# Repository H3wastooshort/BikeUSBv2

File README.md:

# BikeUSB v2 *(WIP)*

Ever wanted to charge your phone of your bikes dynamo?
This Project does just that, for cheap (ish).

## Working Principle
The incoming AC voltage from the dynamo gets rectified by 4 shottky-diodes and buffered in a high-capacity capacitor.
Once a sufficient driving speed is reached and the capacitor is charged enough, the ATtiny1616 MCU on the board wakes up.

It measures the frequency of incoming AC voltage, which is corrolated to the driving speed, until it reaches the first threshold.
Once the first threshold is reached, it can be assumed that enough power is available to charge the phone at 2.5W.
The MCU enables the high efficiency DC/DC-Converter IC to generate 5V at the USB Type C Port.
The pull-ups in the FUSB302 IC are set to signal to the attached device that 2.5W (500mA) are available.
This prevents constant starting and stopping of the charging process, which is annoying.
If the frequency is high enough to reach the 5W or 7.5W thresholds, 5W or 7.5W will be signaled via USB C power delivery.

If the device detects a DC source, it enters configuration mode. In configuration mode, the 2 buttons are used to select which threshold to calibrate.
Connecting it back to a bike dynamo, it is now in calibration mode.
The MCU will detect the needed speed to generate enough power for the prev. selected power level by connecting a 3W, 6W, or 9W constant power load and driving at a steadily increasing speed.
Once the PowerGood signal does not drop out for 5 seconds with the load connected, a sufficient speed has been reached and is saved to EEPROM.

## Schematic

## PCB

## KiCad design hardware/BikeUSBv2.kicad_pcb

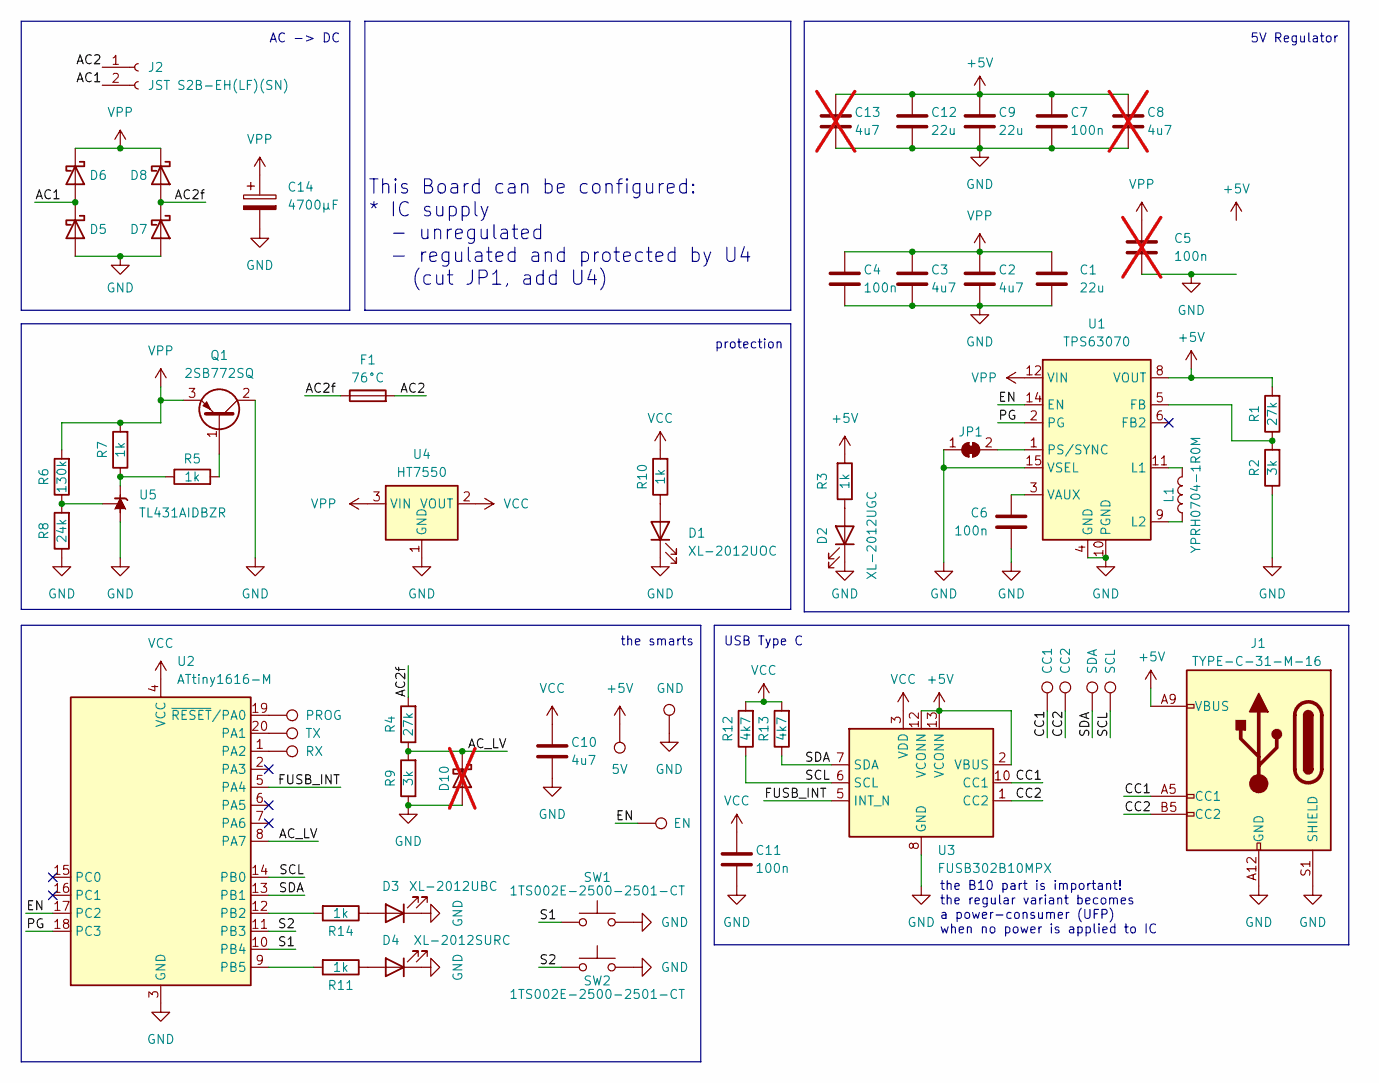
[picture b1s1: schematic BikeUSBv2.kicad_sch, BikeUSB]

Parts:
C1, C9, C12: 22u; C_1206_3216Metric_Pad1.33x1.80mm_HandSolder; LCSC C12891
C2, C3, C10: 4u7; C_0805_2012Metric_Pad1.18x1.45mm_HandSolder; LCSC C1779
C4, C6, C7, C11: 100n; C_0805_2012Metric_Pad1.18x1.45mm_HandSolder; LCSC C1711
C5: 100n; C_0603_1608Metric_Pad1.08x0.95mm_HandSolder; not fitted
C8, C13: 4u7; C_0805_2012Metric_Pad1.18x1.45mm_HandSolder; LCSC C1779; not fitted
C14: 4700µF; CP_Radial_D8.0mm_P5.00mm; LCSC C47893
D1: XL-2012UOC; LED_0805_2012Metric_Pad1.15x1.40mm_HandSolder; LCSC C965813
D2: XL-2012UGC; LED_0805_2012Metric_Pad1.15x1.40mm_HandSolder; LCSC C965815
D3: XL-2012UBC; LED_0805_2012Metric_Pad1.15x1.40mm_HandSolder; LCSC C965817
D4: XL-2012SURC; LED_0805_2012Metric_Pad1.15x1.40mm_HandSolder; LCSC C965812
D5, D6, D7, D8: CMS04(TE12L,Q,M); D_SOD-128; LCSC C603062
D10: D_PowerDI-123; not fitted
F1: 76°C; SETfuse X-Series; Part # X0; LCSC C22396315
J1: TYPE-C-31-M-16; TYPE-C-SMD_TYPE-C-31-M-16; LCSC C283541
J2: JST S2B-EH(LF)(SN); JST_EH_S2B-EH_1x02_P2.50mm_Horizontal; LCSC C514173
JP1: SolderJumper_2_Bridged; SolderJumper-2_P1.3mm_Bridged_RoundedPad1.0x1.5mm
L1: YPRH0704-1R0M; L_7.3x7.3_H4.5; LCSC Part C338840
Q1: 2SB772SQ; SOT-89-3_Handsoldering; LCSC C5158798
R1, R4: 27k; R_0805_2012Metric_Pad1.20x1.40mm_HandSolder; LCSC C375523
R2, R9: 3k; R_0805_2012Metric_Pad1.20x1.40mm_HandSolder; LCSC C218519
R3, R5, R7, R10, R11, R14: 1k; R_0805_2012Metric_Pad1.20x1.40mm_HandSolder; LCSC C110774
R6: 130k; R_0805_2012Metric_Pad1.20x1.40mm_HandSolder; LCSC C2831651
R8: 24k; R_0805_2012Metric_Pad1.20x1.40mm_HandSolder; LCSC C218452
R12, R13: 4k7; R_0805_2012Metric_Pad1.20x1.40mm_HandSolder; LCSC C17673
SW1, SW2: 1TS002E-2500-2501-CT; SW_SPST_CK_RS282G05A3; LCSC C255802
TP1: EN; TestPoint_Pad_D1.0mm
TP2: 5V; TestPoint_Pad_D2.5mm
TP3: GND; TestPoint_Pad_D2.5mm
TP4: PROG; TestPoint_Pad_D2.5mm
TP5: TX; TestPoint_Pad_D2.5mm
TP6: CC1; TestPoint_Pad_D1.5mm
TP7: CC2; TestPoint_Pad_D1.5mm
TP8: SDA; TestPoint_Pad_D1.5mm
TP9: SCL; TestPoint_Pad_D1.5mm
TP10: RX; TestPoint_Pad_D2.5mm
U1: TPS63070; VQFN-HR-15_L3.0-W2.5-P0.50-BL_TPS63070RNMR; LCSC C109322
U2: ATtiny1616-M; VQFN-20-1EP_3x3mm_P0.4mm_EP1.7x1.7mm; LCSC C507118
U3: FUSB302B10MPX; WQFN-14-1EP_2.5x2.5mm_P0.5mm_EP1.45x1.45mm; LCSC C891305
U4: HT7550; SOT-23_Handsoldering; LCSC C5279053
U5: TL431AIDBZR; SOT-23_Handsoldering; LCSC C23892

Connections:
+5V: C7.1, C8.1, C9.1, C12.1, C13.1, J1.A9 (VBUS), J1.B9 (VBUS), R1.2, R3.2, TP2.1, U1.7 (VOUT), U1.8 (VOUT), U3.2 (VBUS), U3.12 (VCONN), U3.13 (VCONN)
/ AC_LV: D10.1 (K), R4.1, R9.2, U2.8 (PA7)
/AC1: D5.1 (K), D6.2 (A), J2.2
/AC2: F1.2, J2.1
/AC2f: D7.1 (K), D8.2 (A), F1.1, R4.2
/CC1: J1.A5 (CC1), TP6.1, U3.10 (CC1), U3.11 (CC1)
/CC2: J1.B5 (CC2), TP7.1, U3.1 (CC2), U3.14 (CC2)
/EN: TP1.1, U1.14 (EN), U2.17 (PC2)
/FUSB_INT: U2.5 (PA4), U3.5 (INT_N)
/PG: U1.2 (PG), U2.18 (PC3)
/S1: SW1.1, U2.10 (PB4)
/S2: SW2.1, U2.11 (PB3)
/SCL: R12.1, TP9.1, U2.14 (PB0), U3.6 (SCL)
/SDA: R13.1, TP8.1, U2.13 (PB1), U3.7 (SDA)
GND: C1.2, C2.2, C3.2, C4.2, C5.2, C6.2, C7.2, C8.2, C9.2, C10.2, C11.2, C12.2, C13.2, C14.2, D1.1 (K), D2.1 (K), D3.1 (K), D4.1 (K), D5.2 (A), D7.2 (A), D10.2 (A), J1.A12 (GND), J1.B12 (GND), J1.S1 (SHIELD), JP1.1 (A), Q1.2 (C), R2.1, R8.1, R9.1, SW1.2, SW2.2, TP3.1, U1.4 (GND), U1.10 (PGND), U1.15 (VSEL), U2.3 (GND), U2.21 (GND), U3.8 (GND), U3.9 (GND), U3.15 (GND), U4.1 (GND), U5.3 (A)
unnamed: D1.2 (A), R10.1
unnamed: D2.2 (A), R3.1
unnamed: D3.2 (A), R14.1
unnamed: D4.2 (A), R11.1
unnamed: JP1.2 (B), U1.1 (PS/SYNC)
unnamed: Q1.1 (B), R5.2
unnamed: R1.1, R2.2, U1.5 (FB)
unnamed: L1.1, U1.11 (L1)
unnamed: L1.2, U1.9 (L2)
unnamed: C6.1, U1.3 (VAUX)
unnamed: TP5.1, U2.20 (PA1)
unnamed: TP10.1, U2.1 (PA2)
unnamed: R14.2, U2.12 (PB2)
unnamed: R11.2, U2.9 (PB5)
unnamed: TP4.1, U2.19 (~RESET/PA0)
unnamed: R5.1, R7.1, U5.1 (K)
unnamed: R6.1, R8.2, U5.2 (REF)
VCC: C10.1, C11.1, R10.2, R12.2, R13.2, U2.4 (VCC), U3.3 (VDD), U3.4 (VDD), U4.2 (VOUT)
VPP: C1.1, C2.1, C3.1, C4.1, C5.1, C14.1, D6.1 (K), D8.1 (K), Q1.3 (E), R6.2, R7.2, U1.12 (VIN), U1.13 (VIN), U4.3 (VIN)

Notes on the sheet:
the smarts
AC -> DC
the B10 part is important! the regular variant becomes a power-consumer (UFP) when no power is applied to IC
USB Type C
5V Regulator
protection
This Board can be configured: * IC supply - unregulated - regulated and protected by U4 (cut JP1, add U4)

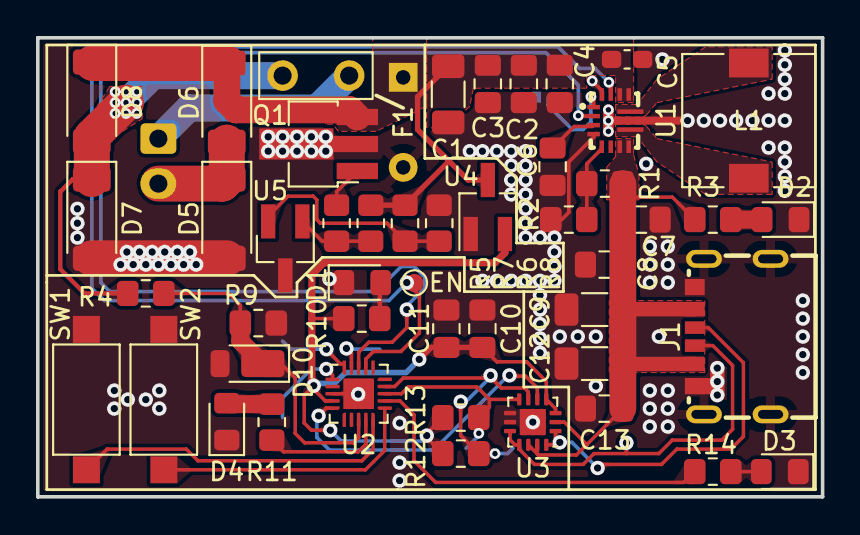
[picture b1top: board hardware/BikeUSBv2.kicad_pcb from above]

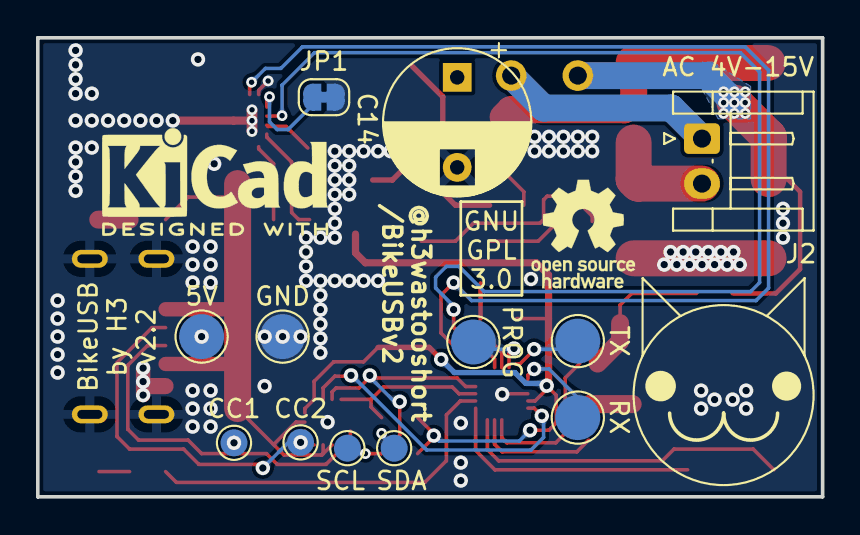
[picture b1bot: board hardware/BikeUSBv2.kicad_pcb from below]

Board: 2 copper layers, 43.6 x 25.5 mm, 61 parts (13 on the bottom side), 34 nets.

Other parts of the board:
CAT**: PCBcat

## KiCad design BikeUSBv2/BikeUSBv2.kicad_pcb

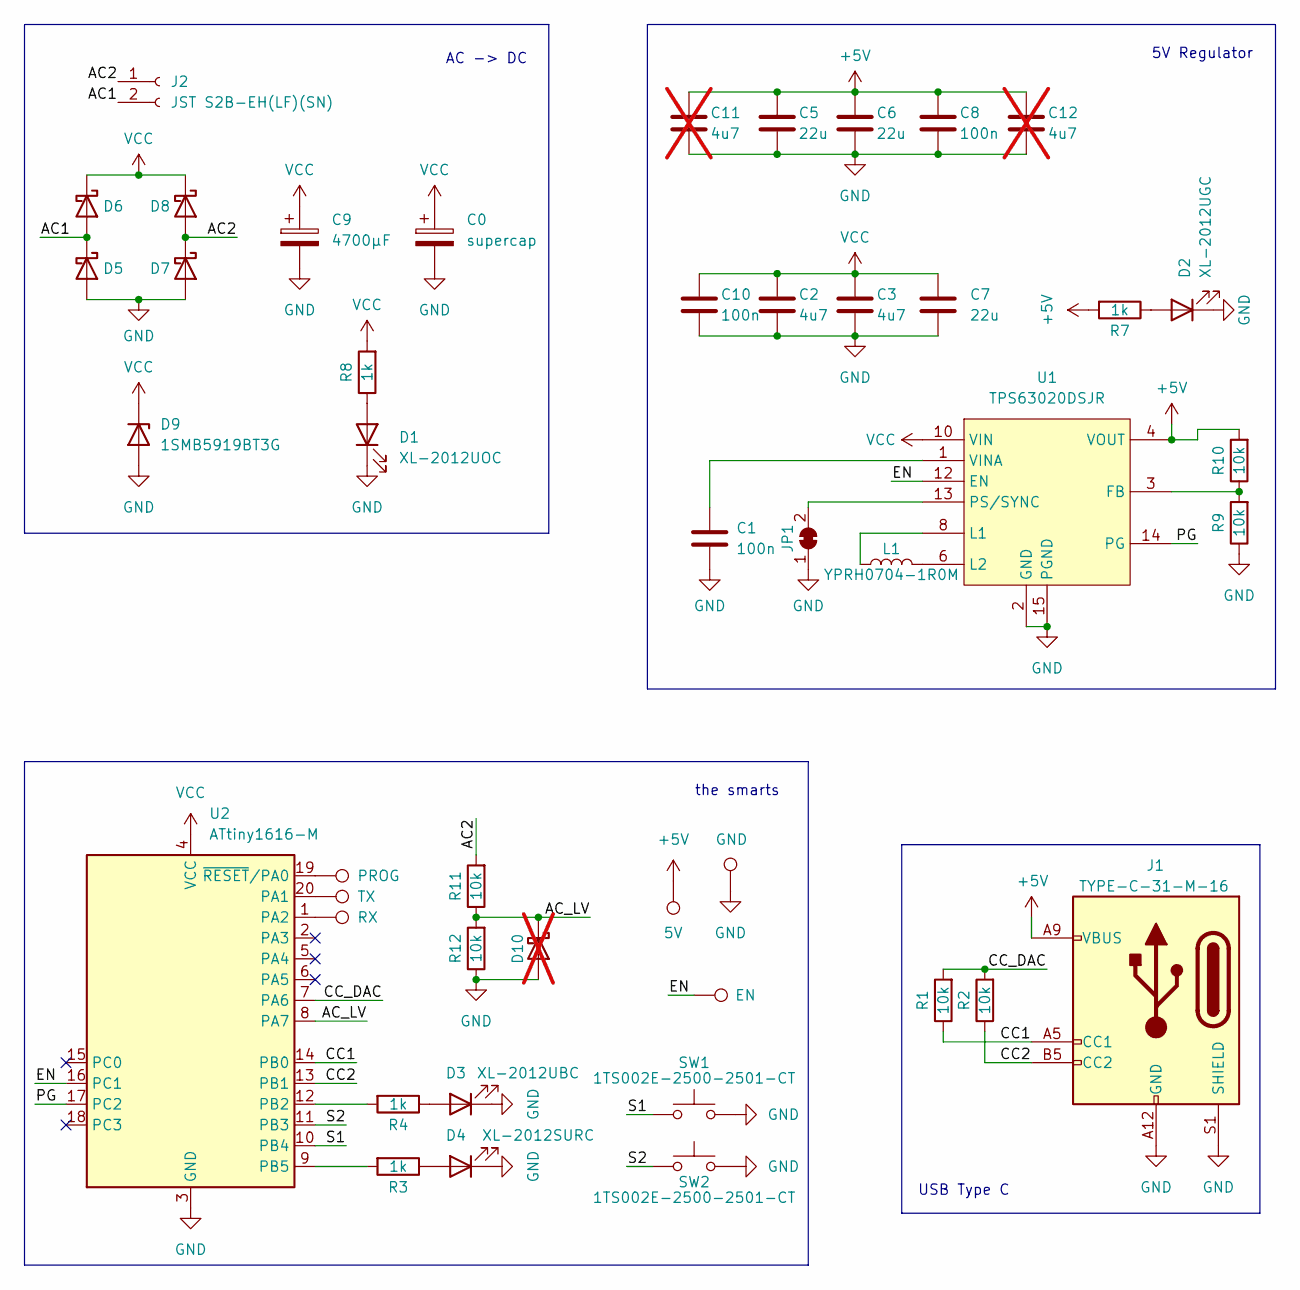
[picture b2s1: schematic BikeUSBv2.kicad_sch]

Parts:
C0: supercap; PinHeader_1x02_P2.54mm_Vertical
C1, C8, C10: 100n; C_0805_2012Metric_Pad1.18x1.45mm_HandSolder; LCSC C1711
C2, C3: 4u7; C_0805_2012Metric_Pad1.18x1.45mm_HandSolder; LCSC C1779
C5, C6, C7: 22u; C_1206_3216Metric_Pad1.33x1.80mm_HandSolder; LCSC C12891
C9: 4700µF; CP_Radial_D8.0mm_P5.00mm; LCSC C47893
C11, C12: 4u7; C_0805_2012Metric_Pad1.18x1.45mm_HandSolder; LCSC C1779; not fitted
D1: XL-2012UOC; LED_0805_2012Metric_Pad1.15x1.40mm_HandSolder; LCSC C965813
D2: XL-2012UGC; LED_0805_2012Metric_Pad1.15x1.40mm_HandSolder; LCSC C965815
D3: XL-2012UBC; LED_0805_2012Metric_Pad1.15x1.40mm_HandSolder; LCSC C965817
D4: XL-2012SURC; LED_0805_2012Metric_Pad1.15x1.40mm_HandSolder; LCSC C965812
D5, D6, D7, D8: CMS04(TE12L,Q,M); D_SOD-128; LCSC C603062
D9: 1SMB5919BT3G; D_SMB-SMC_Universal_Handsoldering; LCSC Part C7422622
D10: D_PowerDI-123; not fitted
J1: TYPE-C-31-M-16; TYPE-C-SMD_TYPE-C-31-M-16; LCSC C283541
J2: JST S2B-EH(LF)(SN); JST_EH_S2B-EH_1x02_P2.50mm_Horizontal; LCSC C514173
JP1: SolderJumper_2_Bridged; SolderJumper-2_P1.3mm_Bridged_RoundedPad1.0x1.5mm
L1: YPRH0704-1R0M; L_7.3x7.3_H4.5; LCSC Part C338840
R1, R2, R9, R10, R11, R12: 10k; R_0805_2012Metric_Pad1.20x1.40mm_HandSolder; LCSC C217770
R3, R4, R7, R8: 1k; R_0805_2012Metric_Pad1.20x1.40mm_HandSolder; LCSC C110774
SW1, SW2: 1TS002E-2500-2501-CT; SW_SPST_CK_RS282G05A3; LCSC C255802
TP1: PROG; TestPoint_Pad_D2.5mm
TP2: GND; TestPoint_Pad_D2.5mm
TP4: TX; TestPoint_Pad_D2.5mm
TP5: RX; TestPoint_Pad_D2.5mm
TP6: 5V; TestPoint_Pad_D2.5mm
TP7: EN; TestPoint_Pad_D2.5mm
U1: TPS63020DSJR; VSON-14_L4.0-W3.0-P0.50-BL-EP_TI_DSJ; LCSC Part C15483
U2: ATtiny1616-M; VQFN-20-1EP_3x3mm_P0.4mm_EP1.7x1.7mm; LCSC C507118

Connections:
+5V: C5.1, C6.1, C8.1, C11.1, C12.1, J1.A9 (VBUS), J1.B9 (VBUS), R7.2, R10.2, TP6.1, U1.4 (VOUT), U1.5 (VOUT)
/ AC_LV: D10.1 (K), R11.1, R12.2, U2.8 (PA7)
/AC1: D5.1 (K), D6.2 (A), J2.2
/AC2: D7.1 (K), D8.2 (A), J2.1, R11.2
/CC1: J1.A5 (CC1), R1.1, U2.14 (PB0)
/CC2: J1.B5 (CC2), R2.1, U2.13 (PB1)
/CC_DAC: R1.2, R2.2, U2.7 (PA6)
/EN: TP7.1, U1.12 (EN), U2.16 (PC1)
/PG: U1.14 (PG), U2.17 (PC2)
/S1: SW1.1, U2.10 (PB4)
/S2: SW2.1, U2.11 (PB3)
GND: C0.2, C1.2, C2.2, C3.2, C5.2, C6.2, C7.2, C8.2, C9.2, C10.2, C11.2, C12.2, D1.1 (K), D2.1 (K), D3.1 (K), D4.1 (K), D5.2 (A), D7.2 (A), D9.2 (A), D10.2 (A), J1.A12 (GND), J1.B12 (GND), J1.S1 (SHIELD), JP1.1 (A), R9.1, R12.1, SW1.2, SW2.2, TP2.1, U1.2 (GND), U1.15 (PGND), U2.3 (GND), U2.21 (GND)
unnamed: D1.2 (A), R8.1
unnamed: D2.2 (A), R7.1
unnamed: D3.2 (A), R4.1
unnamed: D4.2 (A), R3.1
unnamed: JP1.2 (B), U1.13 (PS/SYNC)
unnamed: L1.1, U1.8 (L1), U1.9 (L1)
unnamed: L1.2, U1.6 (L2), U1.7 (L2)
unnamed: R9.2, R10.1, U1.3 (FB)
unnamed: C1.1, U1.1 (VINA)
unnamed: TP4.1, U2.20 (PA1)
unnamed: TP5.1, U2.1 (PA2)
unnamed: R4.2, U2.12 (PB2)
unnamed: R3.2, U2.9 (PB5)
unnamed: TP1.1, U2.19 (~RESET/PA0)
VCC: C0.1, C2.1, C3.1, C7.1, C9.1, C10.1, D6.1 (K), D8.1 (K), D9.1 (K), R8.2, U1.10 (VIN), U1.11 (VIN), U2.4 (VCC)

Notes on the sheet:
the smarts
AC -> DC
USB Type C
5V Regulator

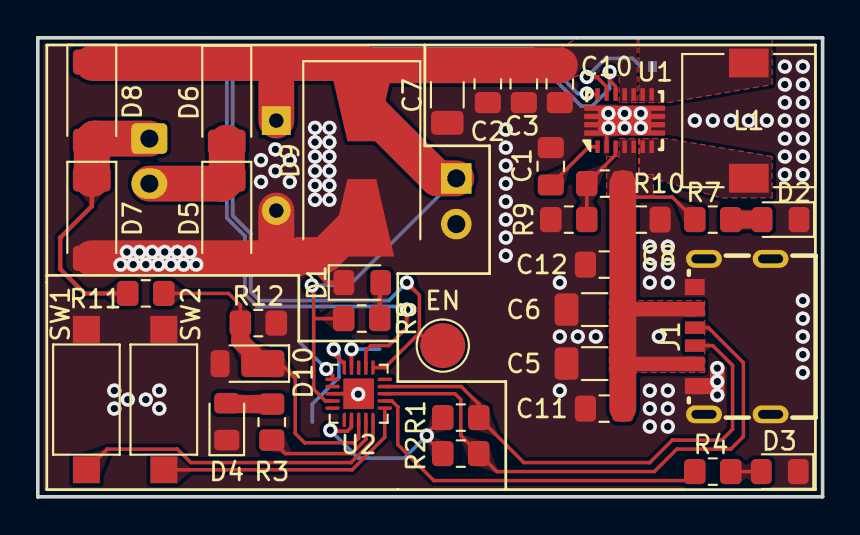
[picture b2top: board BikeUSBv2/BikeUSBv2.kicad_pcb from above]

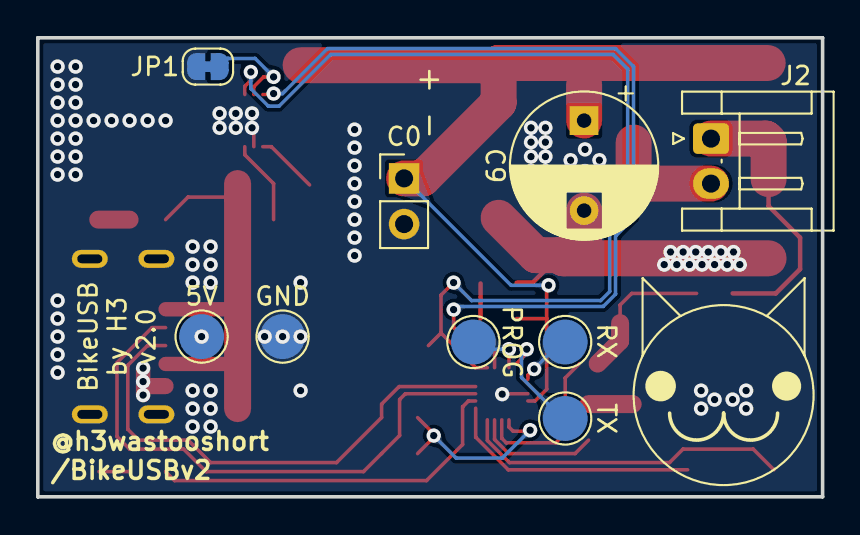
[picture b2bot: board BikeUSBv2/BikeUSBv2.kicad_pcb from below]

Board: 2 copper layers, 43.6 x 25.5 mm, 47 parts (10 on the bottom side), 27 nets.

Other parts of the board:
CAT**: PCBcat

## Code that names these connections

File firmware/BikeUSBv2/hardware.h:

//====PINS====

const uint8_t OUTPUT_ENABLE_PIN = PIN_PC2;
const uint8_t OUTPUT_GOOD_PIN = PIN_PC3;

const uint8_t AC_MEASURE_PIN = PIN_PA7;  //also AINP0, don't change this or AC code must be changed aswell

const uint8_t SDA_PIN = PIN_PC0;
const uint8_t SCL_PIN = PIN_PC1;

const uint8_t FUSB_INT_PIN = PIN_PA4;

#define HAS_FUSB

const uint8_t BTN1_PIN = PIN_PB3;
const uint8_t BTN2_PIN = PIN_PB4;

const uint8_t USR_LED_PIN = PIN_PB5;
const uint8_t PWR_LED_PIN = PIN_PB2;

const uint8_t CC1_PIN = PIN_PB0;
const uint8_t CC2_PIN = PIN_PB1;
const uint8_t CC_DAC_PIN = PIN_PA6;

//====OTHER====

const uint16_t MIN_INPUT_VOLTAGE = 3000;  //in mV, minimum MCU supply voltage needed to allow operation of device
const float FREQ_HYST = 0.1; //10%

//============

void setupHardware() {
  //pin modes
  pinMode(OUTPUT_ENABLE_PIN, OUTPUT);
  digitalWrite(OUTPUT_ENABLE_PIN, LOW);
  pinMode(USR_LED_PIN, OUTPUT);

  //pinMode(AC_MEASURE_PIN, INPUT);
  pinMode(OUTPUT_GOOD_PIN, INPUT_PULLUP);
  pinMode(BTN1_PIN, INPUT_PULLUP);
  pinMode(BTN2_PIN, INPUT_PULLUP);

  pinMode(FUSB_INT_PIN, INPUT_PULLUP);

  //ADC0
  analogReadResolution(10);
  analogReference(INTERNAL2V5);  //set ADC reference to 2.5V as it covers the full range of CC voltages
}

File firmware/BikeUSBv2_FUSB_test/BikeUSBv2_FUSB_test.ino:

#include "../BikeUSBv2/lib/SWI2C_H3/src/SWI2C.h"
#include "../BikeUSBv2/lib/SWI2C_H3/src/SWI2C.cpp"
const uint8_t SDA_PIN = PIN_PC0;
const uint8_t SCL_PIN = PIN_PC1;

const uint8_t FUSB_INT_PIN = PIN_PA4;
SWI2C fusb_i2c(SDA_PIN, SCL_PIN, 0x22);

void setup() {
  // put your setup code here, to run once:
  _PROTECTED_WRITE(WDT.CTRLA, WDT_PERIOD_1KCLK_gc);
  Serial.pins(PIN_PA1, PIN_PA2);
  Serial.begin(9600);
  Serial.println("READY");
}

void loop() {
  // put your main code here, to run repeatedly:
  if (Serial.available()) {
    delay(100);
    switch (Serial.read()) {
      case 'R':
        {
          Serial.println("reading...");
          uint8_t reg = 0, dat = 0xFF;

          reg = Serial.parseInt();

          Serial.printHexln(reg);

          Serial.println(fusb_i2c.readFromRegister(reg, dat) ? "OK" : "FAIL");
          Serial.printHexln(dat);
        }
        break;
      case 'W':
        {
          Serial.println("writing...");

          uint8_t reg = 0, dat = 0;
          reg = Serial.parseInt();
          dat = Serial.parseInt();

          Serial.printHexln(reg);
          Serial.printHexln(dat);

          Serial.println(fusb_i2c.writeToRegister(reg, dat) ? "OK" : "FAIL");
        }
        break;
    }
  }

  __asm__ __volatile__("wdr" ::);
}

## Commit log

2024-01-29 rough schematic
2024-01-29 todia
2024-01-29 some things
2024-01-30 fine, im using an MCU
2024-01-30 group things on PCB
2024-02-02 dont exactly remember what i did here, its from tuesday i think
2024-02-02 placed components, started routing
2024-02-02 routing finished so far
2024-02-03 fix clearances, routing almost done
2024-02-03 idk, forgot to save that
2024-02-03 actually complete routing
2024-02-03 added pcb art, other stuff
2024-02-03 small stuff
2024-02-03 better U1 cap layout
2024-02-03 cleanup
2024-02-03 teardrops
2024-02-03 assign some footprints
2024-02-05 switch diode footprints
2024-02-05 removed teardrops
2024-02-05 added footprint for clamping diode if needed
2024-02-05 reduced component count
2024-02-05 better layout
2024-02-05 stuff
2024-02-05 better inductor track layout
2024-02-05 forgot to rotate the protection silkscreen layer
2024-02-05 oops, those were actually the correct footprints...
2024-02-05 oops 2
2024-02-05 forgot silkscreen
2024-02-05 NPN =/= PNP
2024-02-05 more stuff i forgot
2024-02-05 teardrops + zone fills + other
2024-02-07 update parts
2024-02-07 dingsbumbs
2024-02-07 BOM thing
2024-02-07 all parts selected
2024-02-07 forgot to save PCB
2024-02-08 smaller fixes
2024-02-18 lcsc parts
2024-02-19 half capacitance, but cheaper
2024-02-21 switch CC current source strategy
    these newer attinys have a DAC!
    just use that for the current source!
2024-02-21 push components around, fix lcsc, add cap header
2024-02-22 very small changes
2024-02-22 stop DRC from complaining
2024-02-22 add teardrops
2024-02-27 re-layout parts. routing TBD
2024-02-27 start routing
2024-02-27 route stuff
2024-02-27 routing stuff
2024-03-01 vias, silk
2024-03-15 add docs
2024-03-16 reorder schematic
2024-03-16 fix DRC errors
2024-03-16 auto cleanup
2024-03-16 update docs
2024-03-16 silkscreen
2024-03-17 add name
2024-03-17 rename hardware folder
2024-03-17 add CI
2024-05-05 better auto-img and upload to pages
2024-05-05 fix gha
2024-05-05 fix even dumber issue with gha
2024-05-05 gha names
2024-05-05 fix schematic upload
2024-05-05 fix ghp artifact, split up CI and documentation
2024-05-05 use auto-generated images
2024-05-22 dumb mistake fixed
    i thought the feedback voltage had to be 2.5V at operating voltage. its actually 0.5V
2024-05-22 add proper PD negotiation
2024-05-23 add footprint for ldo-bodge
2024-05-23 oops
2024-05-23 silkscreen cleanup
2024-05-23 clean up teardrops
2024-05-23 different ldo vreg
2024-05-23 switch to FUSB302 without dead-battery charging
2024-05-23 fixup lcsc
2024-05-23 silkscreen fixes
2024-05-23 change OVP protection scheme
2024-05-23 apply changes to PCB
2024-05-23 add info note to sch
2024-05-23 added resistor required in DS
2024-05-23 also render rotating PCB GIF
2024-05-23 remove leftover silkscreen text
2024-05-25 make schematic look nicer
2024-05-25 slight layout improvment
2024-06-12 switch eFuse IC in design
2024-06-13 make U4 optional since new U5 clamps to 5V5
2024-06-13 improve VINA routing
2024-06-13 add therm relief for PTH
2024-06-13 fix stuff like thermals for U5
2024-06-14 layout stuff
2024-06-14 add INT line between U3 and U2
2024-06-14 space EN/PG tracks more + readd teardrops
2024-06-14 forgor
2024-06-14 switch to SOT-23 voltage regulator
2024-06-14 mini silkscreen thing
2024-06-14 add td
2024-06-15 spaghetti diagram
2024-06-15 add submodule for to-be-done FUSB library
2024-06-15 Create led.h
    the most important part of the firmware, the LED blinky stuff!!!!
2024-06-17 move stuff 4 arduino ide
2024-06-17 very very rough idea of how firmware will look
2024-06-17 eeprom check might work now
2024-06-17 wow, this complies
2024-06-20 kinda roughly prototyped MSM
2024-06-20 workin on it
2024-06-20 Summary (required)
2024-06-20 switch I2C library
2024-06-20 Update .gitattributes again, because im stupid
2024-06-20 cal stuff
2024-06-23 experiment with pd stuff
2024-06-23 fix led.h
2024-06-23 fusb code possibly working...
2024-06-23 fgsfd
2024-06-23 change blink patterns
2024-06-27 commit pd friend changes to main program
2024-06-29 pull out src/snk impl. to project code
2024-06-29 pulled out too much
2024-06-29 adapt to pd and msm being indep.
2024-06-29 working on SMs
2024-06-29 cut resistor-based negotiations
    7.5W is pretty unrealistic
    also, I2C needs pullups
2024-06-30 [PCB] change I2C to HW pins
2024-06-30 [PCB] fix Teardrops
2024-06-30 kinda working on it
2024-06-30 interrupt stuff
2024-06-30 pdo stuff
2024-06-30 src stuff
2024-07-01 [PCB] minor layout change
2024-07-01 only enable power after CC pulldowns detected
2024-07-01 [PCB] switch schematic to different VREG
2024-07-01 [PCB] rough layout with new BuckBoost IC
2024-07-01 [PCB] bump version
2024-07-01 [PCB] fix DRC
2024-07-01 [PCB]
    OVP by zener and fuse for now...
2024-07-01 [PCB] different Zener
2024-07-01 [PCB] switch to different protection circuit
2024-07-01 [PCB] add Teardrops
2024-07-01 [PCB] fill in LCSC IDs
2024-07-01 shitty LTSpice sim of voltage limiter
    im assuming the generator won't put out more than 1A
2024-07-01 [PCB] layout less ugly
2024-07-01 [PCB] silk
2024-07-01 [PCB] via changes
    this might help with head conduction from the inductor
2024-07-01 [PCB] changed VREG RDIV for more accurate 5V
    prev 5.13V now 4.98V
2024-07-01 [PCB] small changes
2024-07-02 [PCB] slight sch change
2024-07-02 [PCB] fix DRC, add TD
2024-07-02 [PCB] forgot
2024-07-02 {PCB] geo reannotate
2024-07-02 [PCB] thermal fuse footprint now right pitch
2024-07-02 vlim sim improvments
2024-07-02 rerun pd handshake if power drops out
2024-07-03 [PCB] add solder-covered heatsink surfaces
2024-07-03 [PCB] adjust rendered finish
2024-07-03 [PCB] silkscreen fixes
2024-07-03 [PCB] add voltage rating and OSHW symbol
2024-07-03 [PCB] silk and 3d
2024-07-04 adapt to PD_Friend changes
2024-07-04 add "dumb mode"
2024-07-04 adjust to PD_F changes
2024-07-09 fix pins
2024-07-09 fix serial
2024-07-10 working debug decoder
2024-07-10 decode FUSB registers
2024-07-10 more debug stuff
    aaargh, why can't i even program it via UPDI now?????
2024-07-11 decode error warning
    ahahahahaaaaahahahaaaa there is a 68 Ohm short between UPDI and TX, fucking hell, this is why i could not program it anymore, no clue where tf that short is though, can't see it by eye...
2024-07-11 [PCB] LCSC Numbers
2024-07-11 fix AC RDIV
2024-07-11 [PCB] fix resistors
2024-07-12 idfk
2024-07-12 boot msg
2024-07-12 debug decoder log time
2024-07-12 dd nicer formatting
2024-07-12 better butten handler, fix wdt resets
2024-07-12 btn stuff
2024-07-13 freq measurement
    there is a memory leak somewhere :/
    DBG_FREQ gets printed before DBG_AC, this means AC_new_meas_flag was set high by ????????
2024-07-14 trying to fix memory corruption???
2024-07-14 use more memory-focused CRC library
    EEPROM CRCs now calc correctly, also that memory corruption seems to be gone
2024-07-14 wow im so stupid
    DBG_FREQ and DBG_MSM_STATE has the same ID
2024-07-14 better debug
2024-07-14 fix AC?
2024-07-14 dump config
2024-07-14 freq hyst, fix powerup
2024-07-14 fix p level switching
2024-07-14 calc freq usinsing micros()
2024-07-14 Revert "calc freq usinsing micros()"
    This reverts commit c99cfcac4402f8ccdf8a25f426e3dab792760c7d.
2024-07-14 calculation method switching
2024-07-14 no locking up in cnt freq mode
2024-07-14 shorter AC ISR
2024-07-15 print compiletime aswell
2024-07-16 add debug fw i use
2024-07-16 [PCB] move L1 back to leave more room for U1 heatsink
2024-07-16 i should
2024-07-16 [PCB] add kicad logo and gpl text
2024-07-17 debug failing i2c
2024-07-18 [PCB] move OSHW logo away from via
2024-07-18 [PCB] add CC testpads
2024-07-18 [PCB] move text and such
2024-07-18 debug i2c stretch timeout
2024-07-18 typo
2024-07-21 [PCB] add I2C testpads and improve groundplane
2024-07-21 [PCB] readd teardrops
2024-07-21 unfuck README
2024-07-22 faster makeshift-scope
2024-07-22 avg values
2024-07-22 [PCB] add pullup-resistor for TL431
2024-07-22 [PCB] minor fixes
2024-07-22 [PCB] silkscreen fixes and geographical reannotate
2024-07-22 [PCB] add grounding tab
2024-07-22 add command to set config from serial
2024-07-22 add command prefix
2024-07-23 safer PD state change handling
2024-07-23 more debug and other stuff
2024-08-30 [PCB] also protect diodes
2024-08-30 i did this ages ago
    sig gen now outputs correct hi-frq signal
